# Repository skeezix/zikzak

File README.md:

zikzak
======

Home designed and built retro-inspired computer; build a full computer from scratch, without using modern do-it-all chips

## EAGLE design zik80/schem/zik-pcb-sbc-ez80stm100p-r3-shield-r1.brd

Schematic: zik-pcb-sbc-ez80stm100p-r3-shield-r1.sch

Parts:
3V3OUT, 5OUT: PINHD-1X3; 1X03
BARREL: DCJACKZIK
BOB-PA: PINHD-1X16; 1X16
BOBGPIOB: PINHD-1X8; 1X08
C1, C2, C13: .1uF; C025-025X050
C3: 10uF Tant; C025-025X050
C23: 100uF; C025-025X050
C25: 250uF Pol; E3,5-8
C26: .05uF; C025-025X050
CTSGND: PINHD-1X2; 1X02
FT3V3->PWR3, FT5V->PWR5: PINHD-1X2; 1X02
FTDI: FT232RLSSOP; SSOP28DB
GNDOUT: PINHD-1X3; 1X03
GPIOC-JOY0: PINHD-1X8; 1X08
GPIOD-JOY1: PINHD-1X8; 1X08
HEADPHONE: STEREOHEADPHONEJACK
JOY0, JOY1: DB9FEMALE; DB9
LINEOUT: PINHD-1X2; 1X02
PS2KEYB: PINHD-1X4; 1X04
PS/2KEYB: MINI-DIN6PTH; MINI-DIN6
PWRIN: PINHD-1X4; 1X04
PWROUT: PINHD-1X4; 1X04
R3, R6: 330 ohm; 0204/7
R34: 1K; 0204/7
R37: 10; 0204/7
RXLED: LED5MM
SERSTATE: PINHD-1X6; 1X06
SPKR: PINHD-1X4; 1X04
TPS7133: TPS7133QP; DIL08
TXLED: LED5MM
U$2: MICROSD10
U$3: 10K; POTWHEEL
U$6: LM386-DIP; LM386-DIP8
USBDATA: PINHD-1X5; 1X05
USBGPU: USBMICRO_20329; 4UCONN_20329
USBPORT: PINHD-1X4; 1X04
USBSERPWR: USBMICRO_20329; 4UCONN_20329
VGA1: VGA-F90B; DB-15-F90+SHIELD-BIG_PADS
VGAHDR: PINHD-1X6; 1X06
ZPD0-RXD, ZPD1-TXD: PINHD-1X2; 1X02

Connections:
CTS: CTSGND.2, FTDI.11 (CTS), SERSTATE.6
DCD: FTDI.10 (DCD), SERSTATE.2
DSR: FTDI.9 (DSR), SERSTATE.3
DTR: FTDI.2 (DTR), SERSTATE.4
FTDI3: C1.1, FT3V3->PWR3.1, FTDI.17 (3V3OUT)
GND: BARREL.JACKET (GND), C1.2, C2.2, C3.1, C13.2, CTSGND.1, FTDI.7 (GND7), FTDI.18 (GND18), FTDI.21 (GND21), FTDI.25 (AGND), FTDI.26 (TEST), GNDOUT.1, GNDOUT.2, GNDOUT.3, HEADPHONE.SG (S), JOY0.7, JOY1.7, LINEOUT.1, PS2KEYB.2, PS/2KEYB.3, PWRIN.4, PWROUT.4, R34.2, R37.1, RXLED.K (C), SPKR.4, TPS7133.1, TPS7133.2, TXLED.K (C), U$2.P8 (SD6), U$3.P$2 (CW), U$6.2, U$6.4, USBDATA.5, USBGPU.BASE@1 (GND), USBGPU.BASE@2 (GND), USBGPU.GND, USBGPU.SPRT@1 (GND), USBGPU.SPRT@2 (GND), USBGPU.SPRT@3 (GND), USBGPU.SPRT@4 (GND), USBPORT.4, USBSERPWR.BASE@1 (GND), USBSERPWR.BASE@2 (GND), USBSERPWR.GND, USBSERPWR.SPRT@1 (GND), USBSERPWR.SPRT@2 (GND), USBSERPWR.SPRT@3 (GND), USBSERPWR.SPRT@4 (GND), VGA1.5 (GND), VGA1.6 (VGA-R-), VGA1.7 (VGA-G-), VGA1.8 (VGA-B-), VGA1.10 (GND), VGAHDR.3
unnamed: C23.2, U$3.P$3 (CCW)
unnamed: U$3.P$1 (LO), U$6.3
unnamed: LINEOUT.2, U$6.7
unnamed: R6.2, TXLED.A
unnamed: C23.1, R34.1, SPKR.1, SPKR.2, SPKR.3
unnamed: FTDI.23 (TXLED), R6.1
unnamed: R3.2, RXLED.A
unnamed: FTDI.22 (RXLED), R3.1
unnamed: FTDI.1 (TXD), ZPD1-TXD.1
unnamed: FTDI.5 (RXD), ZPD0-RXD.1
unnamed: C25.+, C26.2, U$6.5
unnamed: C25.-, HEADPHONE.R, HEADPHONE.T
unnamed: C26.1, R37.2
PWR3: 3V3OUT.1, 3V3OUT.2, 3V3OUT.3, C3.2, FT3V3->PWR3.2, PWRIN.3, PWROUT.3, TPS7133.5, TPS7133.6, TPS7133.7, U$2.P6 (SD4)
PWR5: 5OUT.1, 5OUT.2, 5OUT.3, BARREL.CPIN (VCC), C13.1, FT5V->PWR5.2, JOY0.8, JOY1.8, PS2KEYB.3, PS/2KEYB.4, PWRIN.2, PWROUT.2, TPS7133.3, TPS7133.4, U$6.6, USBDATA.1, USBGPU.VBUS, VGA1.9 (+5V)
RI: FTDI.6 (RI), SERSTATE.1
RTS: FTDI.3 (RTS), SERSTATE.5
SB: VGA1.3 (VGA-B), VGAHDR.6
SG: VGA1.2 (VGA-G), VGAHDR.5
SH: VGA1.13 (VGA-HSYNC), VGAHDR.2
SPA0: BOB-PA.1
SPA10: BOB-PA.11, USBDATA.4, USBGPU.ID
SPA11: BOB-PA.12, USBDATA.2, USBGPU.D-
SPA12: BOB-PA.13, USBDATA.3, USBGPU.D+
SR: VGA1.1 (VGA-R), VGAHDR.4
SV: VGA1.14 (VGA-VSYNC), VGAHDR.1
USB5: C2.1, FT5V->PWR5.1, FTDI.4 (VCCIO), FTDI.19 (RESET), FTDI.20 (VCC), USBPORT.1, USBSERPWR.VBUS
USB_D+: FTDI.15 (USBDP), USBPORT.3, USBSERPWR.D+
USB_D-: FTDI.16 (USBDM), USBPORT.2, USBSERPWR.D-
VCC: PWRIN.1, PWROUT.1
ZPB0: BOBGPIOB.1
ZPB2-SS: BOB-PA.5, BOBGPIOB.3, U$2.P4 (SD2)
ZPB3-SCK: BOB-PA.6, BOBGPIOB.4, U$2.P7 (SD5)
ZPB6-MISO: BOB-PA.7, BOBGPIOB.7, U$2.P9 (SD7)
ZPB7-MOSI: BOB-PA.8, BOBGPIOB.8, U$2.P5 (SD3)
ZPC0: GPIOC-JOY0.1, JOY0.5
ZPC1: GPIOC-JOY0.2, JOY0.4
ZPC2: GPIOC-JOY0.3, JOY0.3
ZPC3: GPIOC-JOY0.4, JOY0.2
ZPC4: GPIOC-JOY0.5, JOY0.9
ZPC5: GPIOC-JOY0.6
ZPC6: GPIOC-JOY0.7
ZPC7: GPIOC-JOY0.8
ZPD0: GPIOD-JOY1.1, JOY1.5, ZPD0-RXD.2
ZPD1: GPIOD-JOY1.2, JOY1.4, ZPD1-TXD.2
ZPD2: GPIOD-JOY1.3, JOY1.3
ZPD3: GPIOD-JOY1.4, JOY1.2
ZPD4: GPIOD-JOY1.5, JOY1.9
ZPD5: GPIOD-JOY1.6
ZPD6: GPIOD-JOY1.7
ZPD6_DATA: PS2KEYB.4, PS/2KEYB.1
ZPD7: GPIOD-JOY1.8
ZPD7_CLK: PS2KEYB.1, PS/2KEYB.5

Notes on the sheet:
Optional force CTS to always (gnd)
VBUS D- D+ GND
USB 5V
FTDI OUT 3V3
- NEVER JUMPER enable these unless barrel power jack or headers are unconnected! - Jumper 5V to feed the board from USB (including TPS) - Jump 3V to enable FTDI to feed board; do not do this if TPS7133 is populated
5V->3.3V regulator
header for out.. - VCC - 5 - 3.3 - GND
Power Block
Use Vcc12V or +5?
Audio Amp
Powering PCB Notes
One of: - USB jack, then jumper enable 5v (populated TPS7133) - USB jack, jumper enable 5v and 3v3v (unpopulated TPS7133); pray FTDI can supply enough amp on 3V line - Barrel jack with 5V input brick (populated TPS7133) .. needs TPS - PWRIN header with VCC, 5V, 3V3, GND (unpopulated TPS7133) .. cir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
VCC 5V 3V3 GND
joy up (z80 tx0) joy down (zip rx0) joy left joy right joy fire GND (unused i think actually) ps2 clk ps2 data
joy up joy down joy left joy right joy fire unused I think vblank in frame rdy out
FTDI TX -> mcu RX
FTDI RX -> mcu TX
OTG_FS_ID OTG_FS_DM OTG_FS_DP
Schem pins not same order as physical jack pin order
Checked - ZZ hdr to jack pcb - PS/2 keyb ... ok - SD slot seems okay - JOY0 seems ok - JOY1 seems ok - USB PWR seem ok - USB Data seem ok - vga seems ok - pot wheel seems ok - Barrel ? unchecked, not relevent; probably right, and can specify polarity on male side eventually - headphone .. should be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
SPA4 SPI1 NSS SPA5 SPI1 SCK SPA6 SPI1 MISO SPA7 SPI1 MOSI
NOTE: This connects STM32 SPI1 to eZ80 SPI .. both are GPIO, so one or both side should be highZ mode!
Legend: p1: vsync: B10 p2: hsync: B11 p3: gnd p4: R p5: G p6: B
Should p9 be + or GND? It _can_ power PNP chip in monitor (or monitor can self power.) If monitor self powers and its gnd on board, short wipes board. If pwr on board and or monitor, will monitor handle PNP chip without SPI on cable? Have to assume yes. So we should either not connect the pin at al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
NOTE: SD from eZ80 was added later and can conflict with audio. SD activity shouldn't bother audio but possibly audio will fight with SD..
V+ D- D+ ID GND

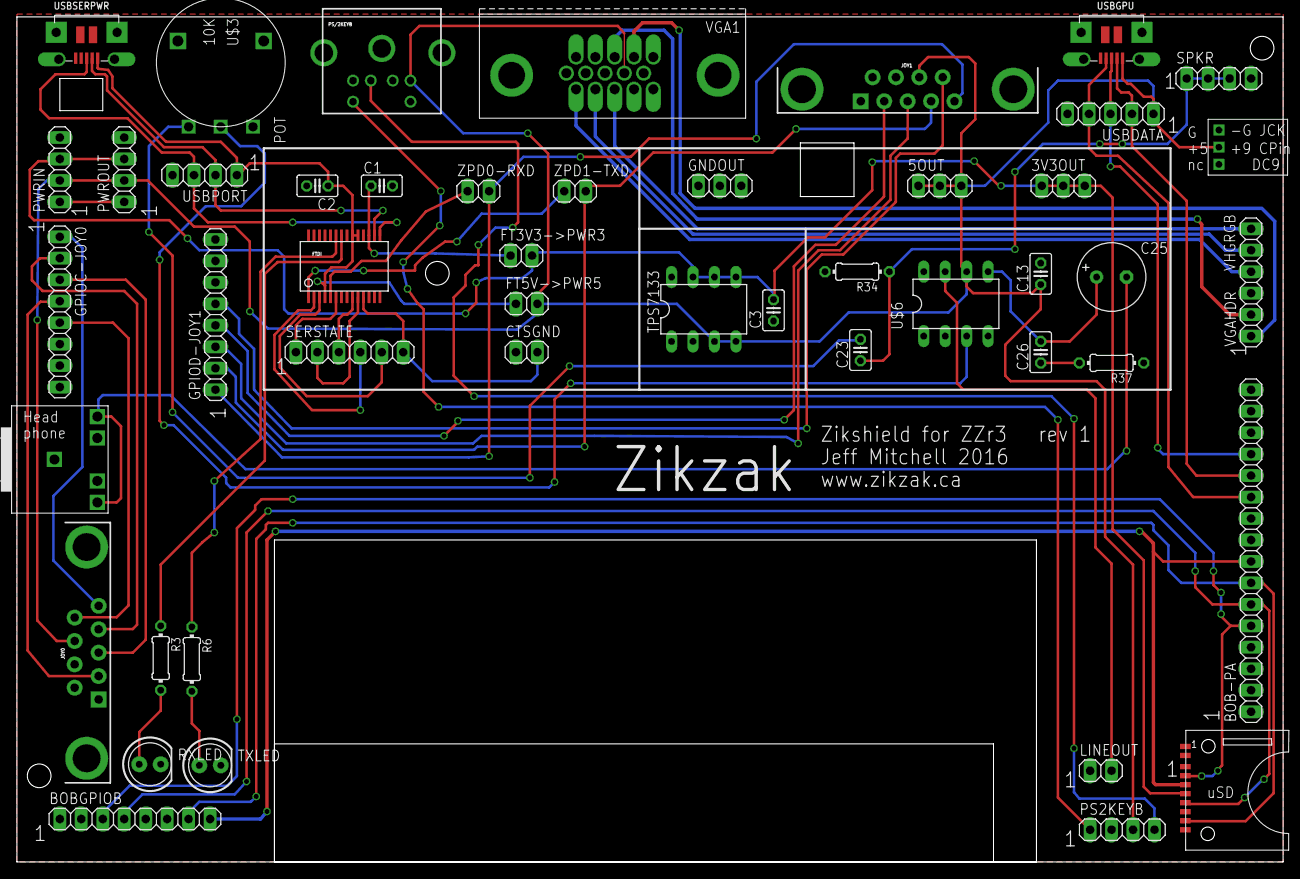
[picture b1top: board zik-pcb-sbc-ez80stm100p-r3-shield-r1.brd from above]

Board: 2 copper layers, 149.8 x 100.0 mm, 47 parts (0 on the bottom side), 51 nets.

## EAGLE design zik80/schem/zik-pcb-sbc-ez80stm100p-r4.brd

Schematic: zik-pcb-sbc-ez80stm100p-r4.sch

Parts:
3V: WIREPADSMD1,27-254; SMD1,27-2,54
+3V3OUT1, +5OUT1: PINHD-1X3; 1X03
+CE2A17: WIREPADSMD1,27-254; SMD1,27-2,54
/CS3: PINHD-1X1; 1X01
AY-3-8913-CS2: AY-3-8912_24PIN-6; DIL24-6
B14, B15: WIREPADSMD1,27-254; SMD1,27-2,54
BOB-PA: PINHD-1X16; 1X16
BOBADDR: PINHD-1X8; 1X08
BOBDATA: PINHD-1X8; 1X08
BOBGPIOB: PINHD-1X8; 1X08
BOBI2C: PINHD-1X2; 1X02
BOBJTAG+: PINHD-1X8; 1X08
BOBMISC: PINHD-1X8; 1X08
C1, C3, C11, C12: 22pF; C025-025X050
C2, C4, C5, C6, C7, C8, C9, C10, C13, C15, C16, C17, C20, C21, C22: .1uF; C025-025X050
C14: ,1uF; C025-025X050
C18, C19: 2.2uF; C025-025X050
C23: 100uF; C025-025X050
C25: 250uF Pol; E3,5-8
C26: .05uF; C025-025X050
CART-CS1: ZIKCART36; ZIKCARTSLOT
D1, D2, D7, D8, D9, D10: 1N4004; DO41-10
EZ80-RESET: SWITCH-MOMENTARY-2PTH; TACTILE-PTH
EZ80F93: EZ80F92AZ; SQFP-S-14X14-100
GNDOUT1: PINHD-1X3; 1X03
GPIOC-JOY0: PINHD-1X8; 1X08
GPIOD-JOY1: PINHD-1X8; 1X08
GPUOSC: 8Mhz; HC49US
IC1: 7432N; DIL14
IC2: 7404N; DIL14
ISPJTAG: PINHD-2X10; 2X10
ISPZDI: PINHD-2X3; 2X03
LED2: LED5MM
LINEOUT: PINHD-1X2; 1X02
OSCDIL14: 2.5MHz; SG51
PHI: PINHD-1X1; 1X01
PS2KEYB: PINHD-1X4; 1X04
PWRIN1: PINHD-1X4; 1X04
PWROUT1: PINHD-1X4; 1X04
R1, R3, R6, R7, R8, R9, R10, R11, R12, R13, R14, R15, R20, R21, R22, R23, R33: 10K; 0204/7
R2: 220 O; 0204/7
R4: 100K; 0204/7
R5, R17, R19, R25, R27, R29, R31: 1K; 0207/10
R16, R18, R24, R28, R30, R32: 2K; 0207/10
R26: 10K; 0207/10
R34: 1K; 0204/7
R36: 10K; PT-10
R37: 10; 0204/7
RAM-CS0: AS6C1008-55PCN; DIP254P1524X393-32
STM32F4: STM32F407V; TQFP100
STM-RESET: SWITCH-MOMENTARY-2PTH; TACTILE-PTH
U$1: LM386-DIP; LM386-DIP8
VBATPWRJP: PINHD-1X2; 1X02
VGAHDR: PINHD-1X6; 1X06
Z-OSC: 20Mhz; HC49US

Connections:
+3V3: 3V.1, +3V3OUT1.1, +3V3OUT1.2, +3V3OUT1.3, C2.1, C4.1, C5.1, C6.1, C7.1, C8.1, C9.1, C10.1, C13.1, C14.1, C15.1, C16.1, C17.1, C20.1, C21.1, C22.1, CART-CS1.PA (VCC33), EZ80F93.7 (+3V3), EZ80F93.18 (+3V3), EZ80F93.33 (+3V3), EZ80F93.43 (+3V3), EZ80F93.50 (WAIT), EZ80F93.56 (+3V3), EZ80F93.67 (+3V3), EZ80F93.87 (+3V3), EZ80F93.96 (+3V3), IC1.14 (+3V3), ISPJTAG.1, ISPJTAG.2, ISPZDI.1, PWRIN1.3, PWROUT1.3, R1.1, R3.2, R6.1, R12.1, R13.1, RAM-CS0.32 (VCC), STM32F4.11 (VDD_1), STM32F4.19 (VDD_2), STM32F4.21 (VREF+), STM32F4.22 (VDDA), STM32F4.28 (VDD_3), STM32F4.50 (VDD_4), STM32F4.75 (VDD_5), STM32F4.100 (VDD_6), VBATPWRJP.2
+5V: +5OUT1.1, +5OUT1.2, +5OUT1.3, AY-3-8913-CS2.13 (VCC), AY-3-8913-CS2.21 (/RESET), AY-3-8913-CS2.23 (A8), CART-CS1.P1 (VCC5), IC2.14 (+5V), OSCDIL14.14 (VDD), PS2KEYB.3, PWRIN1.2, PWROUT1.2, R5.1, R7.2, R8.2, R9.2, R10.2, R11.2, R14.2, R15.2, R20.2, R21.2, R22.2, R23.2, R33.2, U$1.6
+CS2: IC2.2 (O)
+MEMWRITE: AY-3-8913-CS2.2 (BDIR), IC2.4 (O)
/BUSACK: EZ80F93.54 (BUSACK), STM32F4.96 (PB9/TIM11_CH1(5T))
/BUSREQ: EZ80F93.53 (BUSREQ), STM32F4.95 (PB8/TIM10_CH1(5T))
/CS0: EZ80F93.29 (CS0), RAM-CS0.22 (CE), STM32F4.37 (PB2/BOOT1(5T))
/CS1: CART-CS1.PR (/CE), EZ80F93.30 (CS1), ISPJTAG.13, STM32F4.89 (PB3/JTDO(5T))
/CS2: AY-3-8913-CS2.24 (/CS), EZ80F93.31 (CS2), IC2.1 (I), STM32F4.90 (PB4/JNTRST(5T))
/CS3: /CS3.1, EZ80F93.32 (CS3), STM32F4.61 (PD14/TIM4_CH3(5T))
/IOREQ: BOBMISC.4, EZ80F93.45 (IORQ), R13.2, STM32F4.62 (PD15/TIM4_CH4(5T))
/MEMREAD: CART-CS1.P17 (/OE), IC1.6 (O), RAM-CS0.24 (OE), STM32F4.35 (PB0/ETH_MII_RXD2/ADC12_IN8(5T))
/MEMWRITE: CART-CS1.PQ (/WE), IC1.3 (O), IC2.3 (I), RAM-CS0.29 (WE), STM32F4.36 (PB1/ETH_MII_RXD3/ADC12_IN9(5T))
/MREQ: EZ80F93.46 (MREQ), IC1.2 (I1), IC1.4 (I0), STM32F4.91 (PB5/TIM3_CH2(5T))
/RD: BOBMISC.3, EZ80F93.47 (RD), IC1.5 (I1)
/WR: BOBMISC.5, EZ80F93.48 (WR), IC1.1 (I0)
A0: AY-3-8913-CS2.3 (BC1), BOBADDR.1, CART-CS1.PL (A0), EZ80F93.1 (A0), RAM-CS0.12 (A0), STM32F4.97 (PE0(5T))
A1: BOBADDR.2, CART-CS1.PK (A1), EZ80F93.2 (A1), RAM-CS0.11 (A1), STM32F4.98 (PE1(5T))
A2: BOBADDR.3, CART-CS1.PJ (A2), EZ80F93.3 (A2), RAM-CS0.10 (A2), STM32F4.1 (PE2/ETH_MII_TXD3(5T))
A3: BOBADDR.4, CART-CS1.PI (A3), EZ80F93.4 (A3), RAM-CS0.9 (A3), STM32F4.2 (PE3(5T))
A4: BOBADDR.5, CART-CS1.PH (A4), EZ80F93.5 (A4), RAM-CS0.8 (A4), STM32F4.3 (PE4(5T))
A5: BOBADDR.6, CART-CS1.PG (A5), EZ80F93.6 (A5), RAM-CS0.7 (A5), STM32F4.4 (PE5/TIM9_CH1(5T))
A6: BOBADDR.7, CART-CS1.PF (A6), EZ80F93.9 (A6), RAM-CS0.6 (A6), STM32F4.5 (PE6/TIM9_CH2(5T))
A7: BOBADDR.8, CART-CS1.PE (A7), EZ80F93.10 (A7), RAM-CS0.5 (A7), STM32F4.38 (PE7/TIM1_ETR(5T))
A8: CART-CS1.PD (A8), EZ80F93.11 (A8), RAM-CS0.27 (A8), STM32F4.39 (PE8/TIM1_CH1N(5T))
A9: CART-CS1.PC (A9), EZ80F93.12 (A9), RAM-CS0.26 (A9), STM32F4.40 (PE9/TIM1_CH1(5T))
A10: CART-CS1.PB (A10), EZ80F93.13 (A10), RAM-CS0.23 (A10), STM32F4.41 (PE10/TIM1_CH2N(5T))
A11: CART-CS1.P2 (A11), EZ80F93.14 (A11), RAM-CS0.25 (A11), STM32F4.42 (PE11/TIM1_CH2(5T))
A12: CART-CS1.P3 (A12), EZ80F93.15 (A12), RAM-CS0.4 (A12), STM32F4.43 (PE12/TIM1_CH3N(5T))
A13: CART-CS1.P4 (A13), EZ80F93.16 (A13), RAM-CS0.28 (A13), STM32F4.44 (PE13/TIM1_CH3(5T))
A14: CART-CS1.P5 (A14), EZ80F93.17 (A14), RAM-CS0.3 (A14), STM32F4.45 (PE14/TIM1_CH4(5T))
A15: CART-CS1.P6 (A15), EZ80F93.20 (A15), RAM-CS0.31 (A15), STM32F4.46 (PE15/TIM1_BKIN(5T))
A16: CART-CS1.P7 (A16), EZ80F93.21 (A16), RAM-CS0.2 (A16), STM32F4.55 (PD8/USART3_TX(5T))
A17: +CE2A17.1, CART-CS1.P8 (A17), EZ80F93.22 (A17), RAM-CS0.30 (CE2), STM32F4.56 (PD9/USART3_RX(5T))
A18: CART-CS1.P9 (A18), EZ80F93.23 (A18), RAM-CS0.1 (NC), STM32F4.57 (PD10(5T))
A19: CART-CS1.P10 (A19), EZ80F93.24 (A19), STM32F4.58 (PD11(5T))
A20: CART-CS1.P11 (A20), EZ80F93.25 (A20), STM32F4.59 (PD12/TIM4_CH1(5T))
A21: CART-CS1.P12 (A21), EZ80F93.26 (A21), STM32F4.60 (PD13/TIM4_CH2(5T))
A22: EZ80F93.27 (A22)
A23: EZ80F93.28 (A23)
BOOT0: R26.2, STM32F4.94 (BOOT0)
D0: BOBDATA.1, CART-CS1.PM (D0), EZ80F93.35 (D0), RAM-CS0.13 (DQ0), STM32F4.81 (PD0/CAN1_RX(5T))
D1: BOBDATA.2, CART-CS1.PN (D1), EZ80F93.36 (D1), RAM-CS0.14 (DQ1), STM32F4.82 (PD1/CAN1_TX(5T))
D2: BOBDATA.3, CART-CS1.PO (D2), EZ80F93.37 (D2), RAM-CS0.15 (DQ2), STM32F4.83 (PD2/UART5_RX(5T))
D3: BOBDATA.4, CART-CS1.PP (D3), EZ80F93.38 (D3), RAM-CS0.17 (DQ3), STM32F4.84 (PD3(5T))
D4: BOBDATA.5, CART-CS1.P16 (D4), EZ80F93.39 (D4), RAM-CS0.18 (DQ4), STM32F4.85 (PD4(5T))
D5: BOBDATA.6, CART-CS1.P15 (D5), EZ80F93.40 (D5), RAM-CS0.19 (DQ5), STM32F4.86 (PD5/USART2_TX(5T))
D6: BOBDATA.7, CART-CS1.P14 (D6), EZ80F93.41 (D6), RAM-CS0.20 (DQ6), STM32F4.87 (PD6/USART2_RX(5T))
D7: BOBDATA.8, CART-CS1.P13 (D7), EZ80F93.42 (D7), RAM-CS0.21 (DQ7), STM32F4.88 (PD7(5T))
GND: AY-3-8913-CS2.1 (VSS), AY-3-8913-CS2.19 (VSS2), AY-3-8913-CS2.22 (/A9), BOBJTAG+.6, C1.2, C2.2, C3.2, C4.2, C5.2, C6.2, C7.2, C8.2, C9.2, C10.2, C11.2, C12.2, C13.2, C14.2, C15.2, C16.2, C17.2, C18.2, C19.2, C20.2, C21.2, C22.2, CART-CS1.P18 (GND), EZ80-RESET.1, EZ80F93.8 (GND), EZ80F93.19 (GND), EZ80F93.34 (GND), EZ80F93.44 (GND), EZ80F93.57 (GND), EZ80F93.61 (GND), EZ80F93.84 (GND), EZ80F93.97 (GND), GNDOUT1.1, GNDOUT1.2, GNDOUT1.3, IC1.7 (GND), IC1.9 (I0), IC1.10 (I1), IC1.12 (I0), IC1.13 (I1), IC2.5 (I), IC2.7 (GND), IC2.9 (I), IC2.11 (I), IC2.13 (I), ISPJTAG.3, ISPJTAG.12, ISPJTAG.14, ISPJTAG.18, ISPJTAG.20, ISPZDI.3, ISPZDI.5, LED2.K (C), LINEOUT.1, OSCDIL14.7 (VSS), PS2KEYB.2, PWRIN1.4, PWROUT1.4, R26.1, R34.2, R36.2, R37.1, RAM-CS0.16 (VSS), STM32F4.10 (VSS_1), STM32F4.20 (VSSA), STM32F4.27 (VSS_2), STM32F4.74 (VSS_3), STM32F4.99 (VSS_4), STM-RESET.1, U$1.2, U$1.4, VGAHDR.3
HALT_SLP: BOBMISC.2, EZ80F93.55 (HALT_SLP)
unnamed: C3.1, R2.2, R4.2, Z-OSC.2
unnamed: LED2.A, R5.2
unnamed: LINEOUT.2, U$1.7
unnamed: R24.2, R25.2, R31.2, R32.2, VGAHDR.6
unnamed: R18.2, R19.2, R29.2, R30.2, VGAHDR.5
unnamed: D7.C, R27.1
unnamed: D8.C, R28.1
unnamed: C23.2, R36.1
unnamed: R36.3, U$1.3
unnamed: AY-3-8913-CS2.20 (CLK), OSCDIL14.8 (OUT)
unnamed: R16.2, R17.2, R27.2, R28.2, VGAHDR.4
unnamed: D9.C, R29.1
unnamed: D10.C, R30.1
unnamed: D1.C, R31.1
unnamed: D2.C, R32.1
unnamed: C25.+, C26.2, U$1.5
unnamed: C26.1, R37.2
unnamed: AY-3-8913-CS2.15 (CHANNEL_B), AY-3-8913-CS2.17 (CHANNEL_A), AY-3-8913-CS2.18 (CHANNEL_C), C23.1, R34.1
NMI: BOBMISC.1, EZ80F93.52 (NMI), R12.2
NRST: ISPJTAG.15, STM32F4.14 (NRST), STM-RESET.3 (2)
PA0: BOB-PA.1, STM32F4.23 (PA0/ETH_MII_CRS/ADC123_IN0(5T))
PA1: BOB-PA.2, STM32F4.24 (PA1/ETH_RMII_RX_CLK/ADC123_IN1(5T))
PA2: BOB-PA.3, STM32F4.25 (PA2/ETH_MDIO/ADC123_IN2(5T))
PA3: BOB-PA.4, STM32F4.26 (PA3/ETH_MII_COL/ADC123_IN2(5T))
PA4: BOB-PA.5, STM32F4.29 (PA4/ADC12_IN4)
PA5: BOB-PA.6, STM32F4.30 (PA5/SPI1_SCK/ADC12_IN5)
PA6: BOB-PA.7, STM32F4.31 (PA6/SPI1_MISO/ADC12_IN6(5T))
PA7: BOB-PA.8, STM32F4.32 (PA7/ETH_MII_RX_DV/ADC12_IN7(5T))
PA8: BOB-PA.9, STM32F4.67 (PA8/MCO1(5T))
PA9: BOB-PA.10, STM32F4.68 (PA9/USART1_TX(5T))
PA10: BOB-PA.11, STM32F4.69 (PA10/USART1_RX(5T))
PA11: BOB-PA.12, STM32F4.70 (PA11/USART1_CTS(5T))
PA12: BOB-PA.13, STM32F4.71 (PA12/USART1_RTS(5T))
PA13: BOB-PA.14, ISPJTAG.7, STM32F4.72 (PA13/JTMS-SWDAT(5T))
PA14: BOB-PA.15, ISPJTAG.9, STM32F4.76 (PA14/JTCK-SWCLK(5T))
PA15: BOB-PA.16, ISPJTAG.5, STM32F4.77 (PA15/JTDI(5T))
PB6: STM32F4.92 (PB6/I2C1_SCL(5T))
PB7: STM32F4.93 (PB7/I2C1_SDA(5T))
PB10: STM32F4.47 (PB10/ETH_MII_RX_ER(5T)), VGAHDR.1
PB11: STM32F4.48 (PB11/ETH_MII_TX_EN(5T)), VGAHDR.2
PB14: B14.1, STM32F4.53 (PB14/TIM8_CH2N(5T))
PB15: B15.1, STM32F4.54 (PB15/TIM8_CH3N(5T))
PC0: R17.1, STM32F4.15 (PC0/ADC123_IN10(5T))
PC1: R16.1, STM32F4.16 (PC1/ETH_MDC/ADC123_IN11(5T))
PC2: R19.1, STM32F4.17 (PC2/ETH_MII_TXD2/ADC123_IN12(5T))
PC3: R18.1, STM32F4.18 (PC3/ETH_MII_TX_CLK/ADC123_IN13(5T))
PC4: R25.1, STM32F4.33 (PC4/ETH_MII_RXD0/ADC12_IN14(5T))
PC5: R24.1, STM32F4.34 (PC5/ETH_MII_RXD1/ADC12_IN15(5T))
PC6: D1.A, D7.A, D9.A, STM32F4.63 (PC6/TIM3_CH1(5T))
PC7: D2.A, D8.A, D10.A, STM32F4.64 (PC7/TIM8_CH2(5T))
PC8: STM32F4.65 (PC8/TIM8_CH3(5T))
PC9: STM32F4.66 (PC9/TIM3_CH4(5T))
PC10: STM32F4.78 (PC10/UART4_TX(5T))
PC11: STM32F4.79 (PC11/UART4_RX(5T))
PC12: STM32F4.80 (PC12/UART5_TX(5T))
PC13: STM32F4.7 (PC13(5T))
PC14: STM32F4.8 (PC14/OSC32_IN(5T))
PC15: STM32F4.9 (PC15/OSC32_OUT(5T))
PH0: C12.1, GPUOSC.2, STM32F4.12 (PH0-OSC_IN(5T))
PH1: C11.1, GPUOSC.1, STM32F4.13 (PH1-OSC_OUT(5T))
PHI: EZ80F93.100 (PHI), PHI.1
RTC_VDD: BOBMISC.6, EZ80F93.60 (RTC_VDD)
RTC_XIN: BOBMISC.8, EZ80F93.58 (RTC_XIN)
RTC_XOUT: BOBMISC.7, EZ80F93.59 (RTC_XOUT)
SCL: BOBI2C.1, EZ80F93.99 (SCL)
SDA: BOBI2C.2, EZ80F93.98 (SDA)
TCK_ZCL: BOBJTAG+.1, EZ80F93.63 (TCK/ZCL), ISPZDI.4, R1.2
TDI_ZDA: BOBJTAG+.3, EZ80F93.65 (TDI/ZDA), ISPZDI.6, R6.2
TDO: BOBJTAG+.4, EZ80F93.66 (TDO)
TMS: BOBJTAG+.2, EZ80F93.62 (TMS)
TRIGOUT: BOBJTAG+.5, EZ80F93.64 (TRIGOUT)
VBAT: STM32F4.6 (VBAT), VBATPWRJP.1
VCAP_1: C19.1, STM32F4.49 (VCAP1)
VCAP_2: C18.1, STM32F4.73 (VCAP2)
VCC: PWRIN1.1, PWROUT1.1
XIN: C1.1, EZ80F93.85 (XIN), R4.1, Z-OSC.1
XOUT: EZ80F93.86 (XOUT), R2.1
ZNRST: EZ80-RESET.3 (2), EZ80F93.51 (RESET), R3.1
ZPB0: AY-3-8913-CS2.11 (DA0), BOBGPIOB.1, EZ80F93.88 (PB0/T0_IN)
ZPB1: AY-3-8913-CS2.10 (DA1), BOBGPIOB.2, EZ80F93.89 (PB1/T1_IN)
ZPB2: AY-3-8913-CS2.9 (DA2), BOBGPIOB.3, EZ80F93.90 (PB2/SS)
ZPB3: AY-3-8913-CS2.8 (DA3), BOBGPIOB.4, EZ80F93.91 (PB3/SCK)
ZPB4: AY-3-8913-CS2.7 (DA4), BOBGPIOB.5, EZ80F93.92 (PB4/T4_OUT)
ZPB5: AY-3-8913-CS2.6 (DA5), BOBGPIOB.6, EZ80F93.93 (PB5/T5_OUT)
ZPB6: AY-3-8913-CS2.5 (DA6), BOBGPIOB.7, EZ80F93.94 (PB6/MISO)
ZPB7: AY-3-8913-CS2.4 (DA7), BOBGPIOB.8, EZ80F93.95 (PB7/MOSI)
ZPC0: EZ80F93.76 (PC0/TXD1), GPIOC-JOY0.1, R11.1
ZPC1: EZ80F93.77 (PC1/RXD1), GPIOC-JOY0.2, R10.1
ZPC2: EZ80F93.78 (PC2/RTS1), GPIOC-JOY0.3, R9.1
ZPC3: EZ80F93.79 (PC3/CTS1), GPIOC-JOY0.4, R8.1
ZPC4: EZ80F93.80 (PC4/DTR1), GPIOC-JOY0.5, R7.1
ZPC5: EZ80F93.81 (PC5/DSR1), GPIOC-JOY0.6
ZPC6: EZ80F93.82 (PC6/DCD1), GPIOC-JOY0.7, STM32F4.51 (PB12/ETH_MII_TXD0(5T))
ZPC7: EZ80F93.83 (PC7/RI1), GPIOC-JOY0.8, STM32F4.52 (PB13/ETH_MII_TXD1(5T))
ZPD0: EZ80F93.68 (PD0/TXD0), GPIOD-JOY1.1, R23.1
ZPD1: EZ80F93.69 (PD1/RXD0), GPIOD-JOY1.2, R22.1
ZPD2: EZ80F93.70 (PD2/RTS0), GPIOD-JOY1.3, R21.1
ZPD3: EZ80F93.71 (PD3/CTS0), GPIOD-JOY1.4, R20.1
ZPD4: EZ80F93.72 (PD4/DTR0), GPIOD-JOY1.5, R14.1
ZPD5: EZ80F93.73 (PD5/DSR0), GPIOD-JOY1.6
ZPD6: EZ80F93.74 (PD6/DCD0), GPIOD-JOY1.7, PS2KEYB.4, R33.1
ZPD7: EZ80F93.75 (PD7/RI0), GPIOD-JOY1.8, PS2KEYB.1, R15.1

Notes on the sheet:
Power-In header - VCC - 5 - 3.3 - GND
Power LED 5V
Note that GPIO C and D have serial on them; instead of 2nd joystick, use it for serial debugging, forex. Just don't populate the pullup resistors in that case or serial fail.
joy up (z80 tx0) joy down (zip rx0) joy left joy right joy fire2/unused GND ps2 clk ps2 data
joy up joy down joy left joy right joy fire joy fire2 or unused vblank in frame rdy out
Assignments: GPIO PB: audio data bus - when /cs2 audio not active can use GPIOB (or don't populate AY-3-8913) GPIO PC: 6 for joy1 2 for vbl/frameready GPIO PD: 6 for joy-2 2 for keyb
Jeff Mitchell 2014 www.zikzak.ca
.. and lame 1 pin headers, to save me from routing the basketweave.. maybe clean up later
ISP
Power Our duplicates - VCC - 5 - 3.3 - GND
2.2uF = 22pF
Legend: p1: vsync: B10 p2: hsync: B11 p3: gnd p4: R p5: G p6: B
PA2-3 == serial console PA8-PA12 = serial control in/out PB0-5 = ctrl bus OE WE /CS0-2 /mreq NoMore PB6/PB7 = i2c sda/scl PB8 -> ctrl bus BUSREQ PB9 -> ctrl bus BUSACK PB10/11 == sync PB12 -> vblank -> z80 -> ZPC6 PB13 -> frameready in -> z80 PB14/15 -> BoB (USB?) PC0-5 == RGB PC6-7 = brightness PE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
Brightness mix-in RRGGBBXX .. XX being brightness
Resistors are alternating 1K and 2K values
/OE /WE /CS0 ram /CS1 cart rom /CS2 audio /MREQ ez80 /BUSREQ /BUSACK .. /CS3 on PD14 .. /IOREQ on PD15
usart1, usart2, other stuff Console TX (send from micro) to PC: usart2 Console RX (receive to micro) to PC PA8-2 - usart1 --> could jumper to eZ80 GPIO/serial
Of interest.. - Bus expansion: -> /CS3 is on breakout and also to gpu, can be used for expansion of RAM/etc -> SD on GPIO B with SPI from Z? -> ethernet not supposed on eZ80 F92/93 (is on F91), but i2c, spi, serial, etc etc.. -> USB off GPU PA breakout? PB14/15 are open but hard as hell to reach...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
Zikzak SBC - Single board computer Jeff Mitchell 2014
rev 4: Goal: move to sockets on pcb instead of millions of header pins - add mixer hw to audio - add amplifier hw to audio - ?? add SD on pcb? - ?? add USB for direct power? - ?? USB -> ez80? or stm32f4? - ?? newer stm32f5? rev 3: - rotated 180deg ISPZDI - rotated 180deg ISP GPU - Z GPIO-B -> audio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
BoB for PB14/PB15 -> also as USB to savd using PA11/PA12 as USB
ZPD7 -> CLK ZPD6 -> DATA
Diodes are fast low voltage signal diodes; mA is not so important, but fast response time is. Currently trying 1N4148 as widely available and cheap
Vcc typically not used on main board, but could be used for audio amp.. Should be 6-12V .. power board will shift that down to 5 and 3 as needed to feed other pins
Use Vcc12V or +5? Decouple Vcc/GND with a cap?
todo: headphone jack

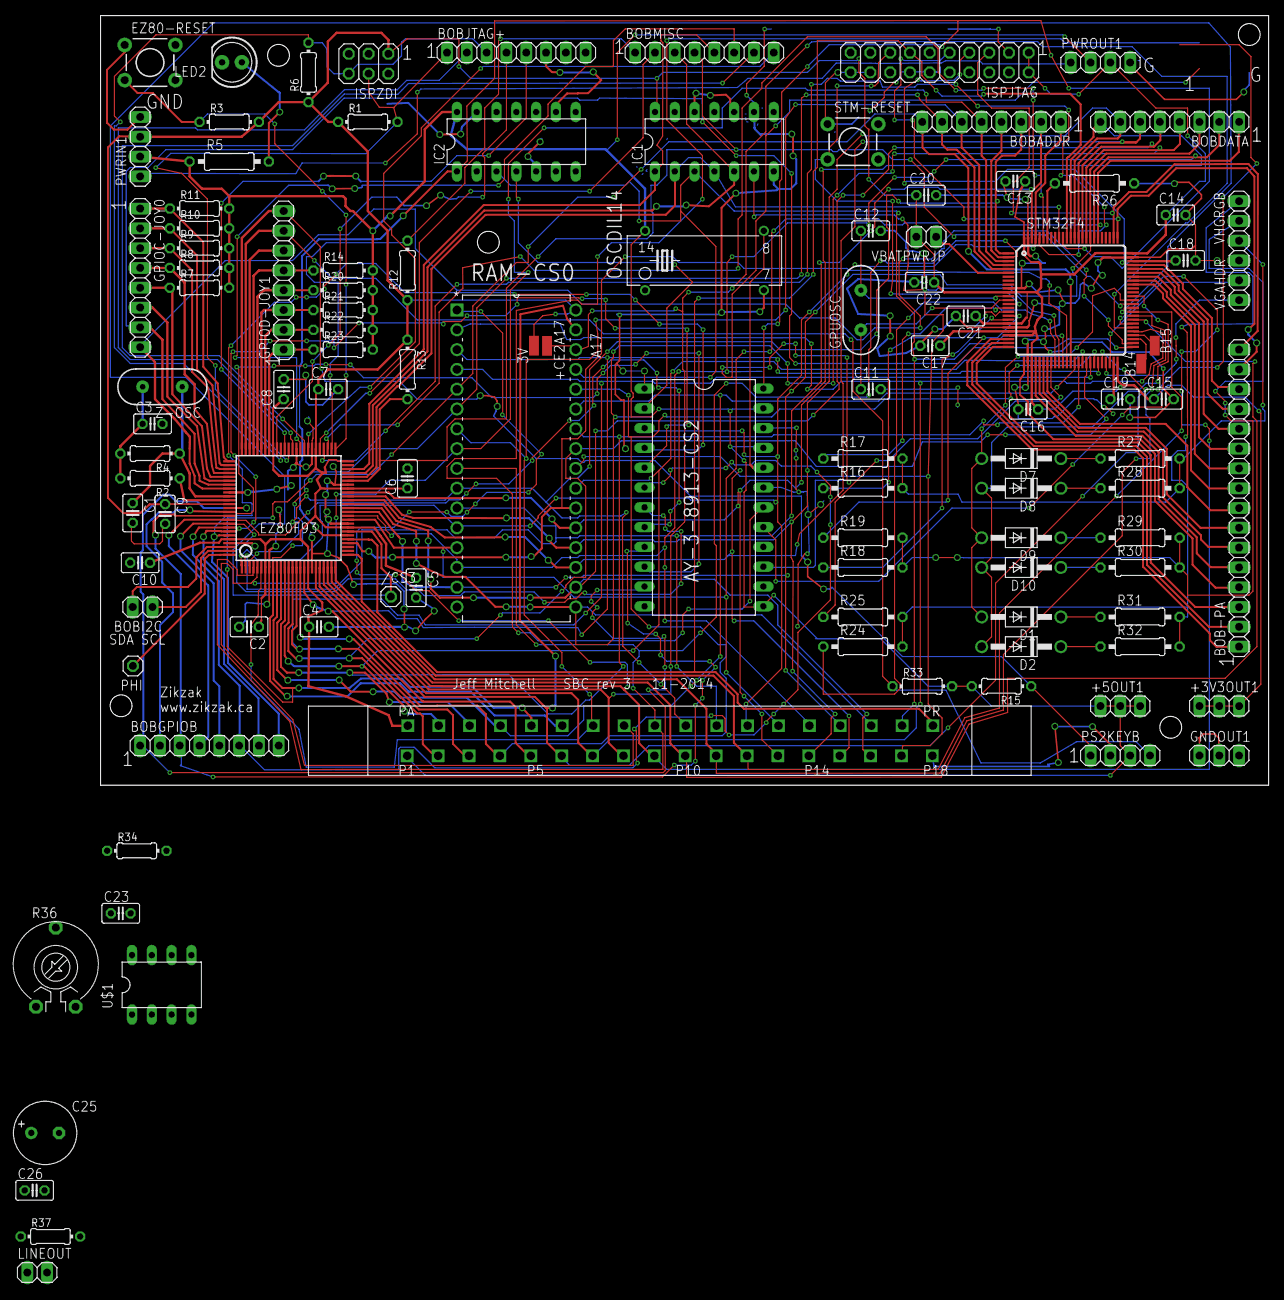
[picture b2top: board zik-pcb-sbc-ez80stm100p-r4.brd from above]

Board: 2 copper layers, 149.8 x 98.7 mm, 107 parts (0 on the bottom side), 140 nets.

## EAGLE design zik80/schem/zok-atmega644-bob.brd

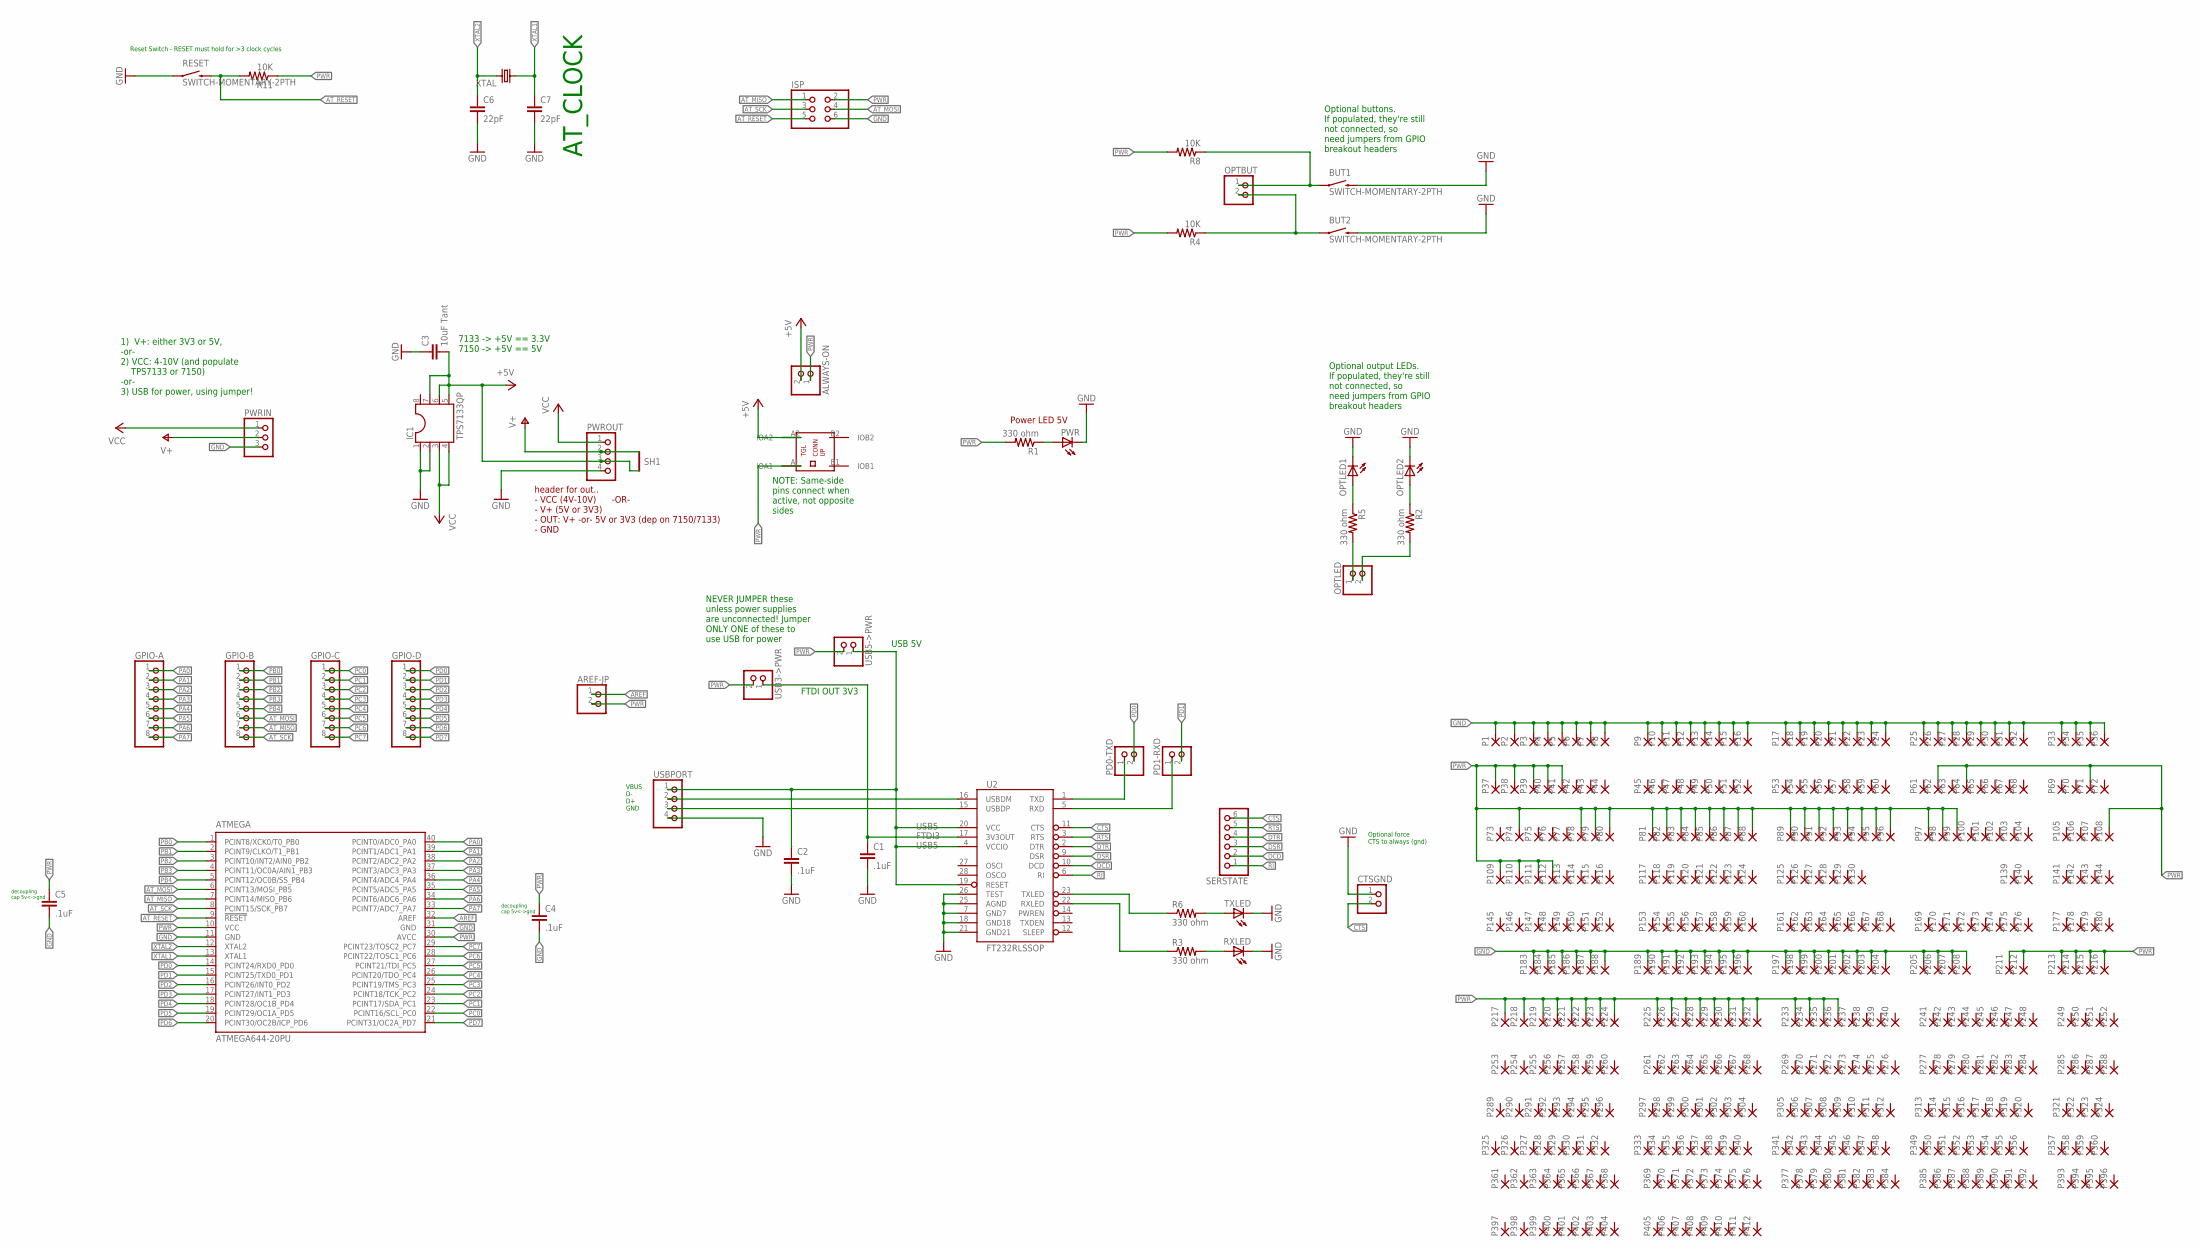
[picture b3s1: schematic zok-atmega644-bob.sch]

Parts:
ALWAYS-ON: PINHD-1X2; 1X02
AREF-JP: PINHD-1X2; 1X02
ATMEGA: ATMEGA644-20PU; DIL40
BUT1, BUT2: SWITCH-MOMENTARY-2PTH; TACTILE-PTH
C1, C2, C4, C5: .1uF; C025-025X050
C3: 10uF Tant; C025-025X050
C6, C7: 22pF; C025-025X050
CTSGND: PINHD-1X2; 1X02
GPIO-A: PINHD-1X8; 1X08
GPIO-B: PINHD-1X8; 1X08
GPIO-C: PINHD-1X8; 1X08
GPIO-D: PINHD-1X8; 1X08
IC1: TPS7133QP; DIL08
ISP: PINHD-2X3; 2X03
OPTBUT: PINHD-1X2; 1X02
OPTLED: PINHD-1X2; 1X02
OPTLED1, OPTLED2: LED5MM
P1, P2, P3, P4, P5, P6, P7, P8, P9, P10, P11, P12, P13, P14, P15, P16, P17, P18, P19, P20, P21, P22, P23, P24, P25, P26, P27, P28, P29, P30, P31, P32, P33, P34, P35, P36, P37, P38, P39, P40, P41, P42, P43, P44, P45, P46, P47, P48, P49, P50, P51, P52, P53, P54, P55, P56, P57, P58, P59, P60, P61, P62, P63, P64, P65, P66, P67, P68, P69, P70, P71, P72, P73, P74, P75, P76, P77, P78, P79, P80, P81, P82, P83, P84, P85, P86, P87, P88, P89, P90, P91, P92, P93, P94, P95, P96, P97, P98, P99, P100, P101, P102, P103, P104, P105, P106, P107, P108, P109, P110, P111, P112, P113, P114, P115, P116, P117, P118, P119, P120, P121, P122, P123, P124, P125, P126, P127, P128, P129, P130, P139, P140, P141, P142, P143, P144, P145, P146, P147, P148, P149, P150, P151, P152, P153, P154, P155, P156, P157, P158, P159, P160, P161, P162, P163, P164, P165, P166, P167, P168, P169, P170, P171, P172, P173, P174, P175, P176, P177, P178, P179, P180, P183, P184, P185, P186, P187, P188, P189, P190, P191, P192, P193, P194, P195, P196, P197, P198, P199, P200, P201, P202, P203, P204, P205, P206, P207, P208, P211, P212, P213, P214, P215, P216, P217, P218, P219, P220, P221, P222, P223, P224, P225, P226, P227, P228, P229, P230, P231, P232, P233, P234, P235, P236, P237, P238, P239, P240, P241, P242, P243, P244, P245, P246, P247, P248, P249, P250, P251, P252, P253, P254, P255, P256, P257, P258, P259, P260, P261, P262, P263, P264, P265, P266, P267, P268, P269, P270, P271, P272, P273, P274, P275, P276, P277, P278, P279, P280, P281, P282, P283, P284, P285, P286, P287, P288, P289, P290, P291, P292, P293, P294, P295, P296, P297, P298, P299, P300, P301, P302, P303, P304, P305, P306, P307, P308, P309, P310, P311, P312, P313, P314, P315, P316, P317, P318, P319, P320, P321, P322, P323, P324, P325, P326, P327, P328, P329, P330, P331, P332, P333, P334, P335, P336, P337, P338, P339, P340, P341, P342, P343, P344, P345, P346, P347, P348, P349, P350, P351, P352, P353, P354, P355, P356, P357, P358, P359, P360, P361, P362, P363, P364, P365, P366, P367, P368, P369, P370, P371, P372, P373, P374, P375, P376, P377, P378, P379, P380, P381, P382, P383, P384, P385, P386, P387, P388, P389, P390, P391, P392, P393, P394, P395, P396, P397, P398, P399, P400, P401, P402, P403, P404, P405, P406, P407, P408, P409, P410, P411, P412: 1,6/0,9
PD0-TXD, PD1-RXD: PINHD-1X2; 1X02
PWR: LED5MM
PWRIN: PINHD-1X3; 1X03
PWROUT: PINHD-1X4; 1X04
R1, R2, R3, R5, R6: 330 ohm; 0204/7
R4, R8, R11: 10K; 0204/7
RESET: SWITCH-MOMENTARY-2PTH; TACTILE-PTH
RXLED: LED5MM
SERSTATE: PINHD-1X6; 1X06
SH1: SHORT-VT5; SHORT_TOP-50
TXLED: LED5MM
U2: FT232RLSSOP; SSOP28DB
U$4: TOGGLE-CYAN-L-ZIK; TOGGLE-CYAN-LG-ZIK
USB3->PWR, USB5->PWR: PINHD-1X2; 1X02
USBPORT: PINHD-1X4; 1X04
XTAL: CRYSTALHC49S; HC49/S

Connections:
+5V: ALWAYS-ON.2, C3.2, IC1.5, IC1.6, IC1.7, PWROUT.3, SH1.1, U$4.A2 (IOA2)
AREF: AREF-JP.1, ATMEGA.32 (AREF)
AT_MISO: ATMEGA.7 (PCINT14/MISO_PB6), GPIO-B.7, ISP.1
AT_MOSI: ATMEGA.6 (PCINT13/MOSI_PB5), GPIO-B.6, ISP.4
AT_RESET: ATMEGA.9 (!RESET), ISP.5, R11.2, RESET.3 (2)
AT_SCK: ATMEGA.8 (PCINT15/SCK_PB7), GPIO-B.8, ISP.3
CTS: CTSGND.2, SERSTATE.6, U2.11 (CTS)
DCD: SERSTATE.2, U2.10 (DCD)
DSR: SERSTATE.3, U2.9 (DSR)
DTR: SERSTATE.4, U2.2 (DTR)
FTDI3: C1.1, U2.17 (3V3OUT), USB3->PWR.1
GND: ATMEGA.11 (GND), ATMEGA.31 (GND), BUT1.3 (2), BUT2.3 (2), C1.2, C2.2, C3.1, C4.2, C5.2, C6.2, C7.2, CTSGND.1, IC1.1, IC1.2, ISP.6, OPTLED1.K (C), OPTLED2.K (C), P1.1, P2.1, P3.1, P4.1, P5.1, P6.1, P7.1, P8.1, P9.1, P10.1, P11.1, P12.1, P13.1, P14.1, P15.1, P16.1, P17.1, P18.1, P19.1, P20.1, P21.1, P22.1, P23.1, P24.1, P25.1, P26.1, P27.1, P28.1, P29.1, P30.1, P31.1, P32.1, P33.1, P34.1, P35.1, P36.1, P183.1, P184.1, P185.1, P186.1, P187.1, P188.1, P189.1, P190.1, P191.1, P192.1, P193.1, P194.1, P195.1, P196.1, P197.1, P198.1, P199.1, P200.1, P201.1, P202.1, P203.1, P204.1, P205.1, P206.1, P207.1, P208.1, PWR.K (C), PWRIN.3, PWROUT.4, RESET.1, RXLED.K (C), TXLED.K (C), U2.7 (GND7), U2.18 (GND18), U2.21 (GND21), U2.25 (AGND), U2.26 (TEST), USBPORT.4
unnamed: BUT1.1, OPTBUT.1, R8.1
unnamed: BUT2.1, OPTBUT.2, R4.1
unnamed: PWR.A, R1.1
unnamed: R6.2, TXLED.A
unnamed: OPTLED.1, R5.2
unnamed: OPTLED2.A, R2.1
unnamed: OPTLED.2, R2.2
unnamed: R6.1, U2.23 (TXLED)
unnamed: OPTLED1.A, R5.1
unnamed: R3.2, RXLED.A
unnamed: R3.1, U2.22 (RXLED)
unnamed: PD0-TXD.1, U2.1 (TXD)
unnamed: PD1-RXD.1, U2.5 (RXD)
PA0: ATMEGA.40 (PCINT0/ADC0_PA0), GPIO-A.1
PA1: ATMEGA.39 (PCINT1/ADC1_PA1), GPIO-A.2
PA2: ATMEGA.38 (PCINT2/ADC2_PA2), GPIO-A.3
PA3: ATMEGA.37 (PCINT3/ADC3_PA3), GPIO-A.4
PA4: ATMEGA.36 (PCINT4/ADC4_PA4), GPIO-A.5
PA5: ATMEGA.35 (PCINT5/ADC5_PA5), GPIO-A.6
PA6: ATMEGA.34 (PCINT6/ADC6_PA6), GPIO-A.7
PA7: ATMEGA.33 (PCINT7/ADC7_PA7), GPIO-A.8
PB0: ATMEGA.1 (PCINT8/XCK0/T0_PB0), GPIO-B.1
PB1: ATMEGA.2 (PCINT9/CLKO/T1_PB1), GPIO-B.2
PB2: ATMEGA.3 (PCINT10/INT2/AIN0_PB2), GPIO-B.3
PB3: ATMEGA.4 (PCINT11/OC0A/AIN1_PB3), GPIO-B.4
PB4: ATMEGA.5 (PCINT12/OC0B/SS_PB4), GPIO-B.5
PC0: ATMEGA.22 (PCINT16/SCL_PC0), GPIO-C.1
PC1: ATMEGA.23 (PCINT17/SDA_PC1), GPIO-C.2
PC2: ATMEGA.24 (PCINT18/TCK_PC2), GPIO-C.3
PC3: ATMEGA.25 (PCINT19/TMS_PC3), GPIO-C.4
PC4: ATMEGA.26 (PCINT20/TDO_PC4), GPIO-C.5
PC5: ATMEGA.27 (PCINT21/TDI_PC5), GPIO-C.6
PC6: ATMEGA.28 (PCINT22/TOSC1_PC6), GPIO-C.7
PC7: ATMEGA.29 (PCINT23/TOSC2_PC7), GPIO-C.8
PD0: ATMEGA.14 (PCINT24/RXD0_PD0), GPIO-D.1, PD0-TXD.2
PD1: ATMEGA.15 (PCINT25/TXD0_PD1), GPIO-D.2, PD1-RXD.2
PD2: ATMEGA.16 (PCINT26/INT0_PD2), GPIO-D.3
PD3: ATMEGA.17 (PCINT27/INT1_PD3), GPIO-D.4
PD4: ATMEGA.18 (PCINT28/OC1B_PD4), GPIO-D.5
PD5: ATMEGA.19 (PCINT29/OC1A_PD5), GPIO-D.6
PD6: ATMEGA.20 (PCINT30/OC2B/ICP_PD6), GPIO-D.7
PD7: ATMEGA.21 (PCINT31/OC2A_PD7), GPIO-D.8
PWR: ALWAYS-ON.1, AREF-JP.2, ATMEGA.10 (VCC), ATMEGA.30 (AVCC), C4.1, C5.1, ISP.2, P37.1, P38.1, P39.1, P40.1, P41.1, P62.1, P64.1, P71.1, P74.1, P78.1, P79.1, P80.1, P81.1, P82.1, P83.1, P84.1, P85.1, P86.1, P87.1, P88.1, P89.1, P90.1, P91.1, P92.1, P93.1, P94.1, P95.1, P96.1, P97.1, P98.1, P99.1, P108.1, P109.1, P110.1, P111.1, P112.1, P211.1, P212.1, P213.1, P214.1, P215.1, P216.1, P217.1, P218.1, P219.1, P220.1, P221.1, P222.1, P223.1, P224.1, P225.1, P226.1, P227.1, P228.1, P229.1, P230.1, P231.1, P232.1, P233.1, P234.1, P235.1, P236.1, R1.2, R4.2, R8.2, R11.1, U$4.A! (IOA1), USB3->PWR.2, USB5->PWR.2
RI: SERSTATE.1, U2.6 (RI)
RTS: SERSTATE.5, U2.3 (RTS)
USB5: C2.1, U2.4 (VCCIO), U2.19 (RESET), U2.20 (VCC), USB5->PWR.1, USBPORT.1
USB_D+: U2.15 (USBDP), USBPORT.3
USB_D-: U2.16 (USBDM), USBPORT.2
V+: PWRIN.2, PWROUT.2, SH1.2
VCC: IC1.3, IC1.4, PWRIN.1, PWROUT.1
XTAL1: ATMEGA.13 (XTAL1), C7.1, XTAL.1
XTAL2: ATMEGA.12 (XTAL2), C6.1, XTAL.2

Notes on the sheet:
Optional force CTS to always (gnd)
header for out.. - VCC (4V-10V) -OR- - V+ (5V or 3V3) - OUT: V+ -or- 5V or 3V3 (dep on 7150/7133) - GND
1) V+: either 3V3 or 5V, -or- 2) VCC: 4-10V (and populate TPS7133 or 7150) -or- 3) USB for power, using jumper!
Power LED 5V
NOTE: Same-side pins connect when active, not opposite sides
7133 -> +5V == 3.3V 7150 -> +5V == 5V
decoupling cap 5v<->gnd
Optional output LEDs. If populated, they're still not connected, so need jumpers from GPIO breakout headers
Reset Switch - RESET must hold for >3 clock cycles
AT_CLOCK
Optional buttons. If populated, they're still not connected, so need jumpers from GPIO breakout headers
VBUS D- D+ GND
USB 5V
FTDI OUT 3V3
NEVER JUMPER these unless power supplies are unconnected! Jumper ONLY ONE of these to use USB for power

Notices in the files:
parts and their libraries:
SparkFun-Electromechanical: Licensing: CC v3.0 Share-Alike You are welcome to use this library for commercial purposes.
